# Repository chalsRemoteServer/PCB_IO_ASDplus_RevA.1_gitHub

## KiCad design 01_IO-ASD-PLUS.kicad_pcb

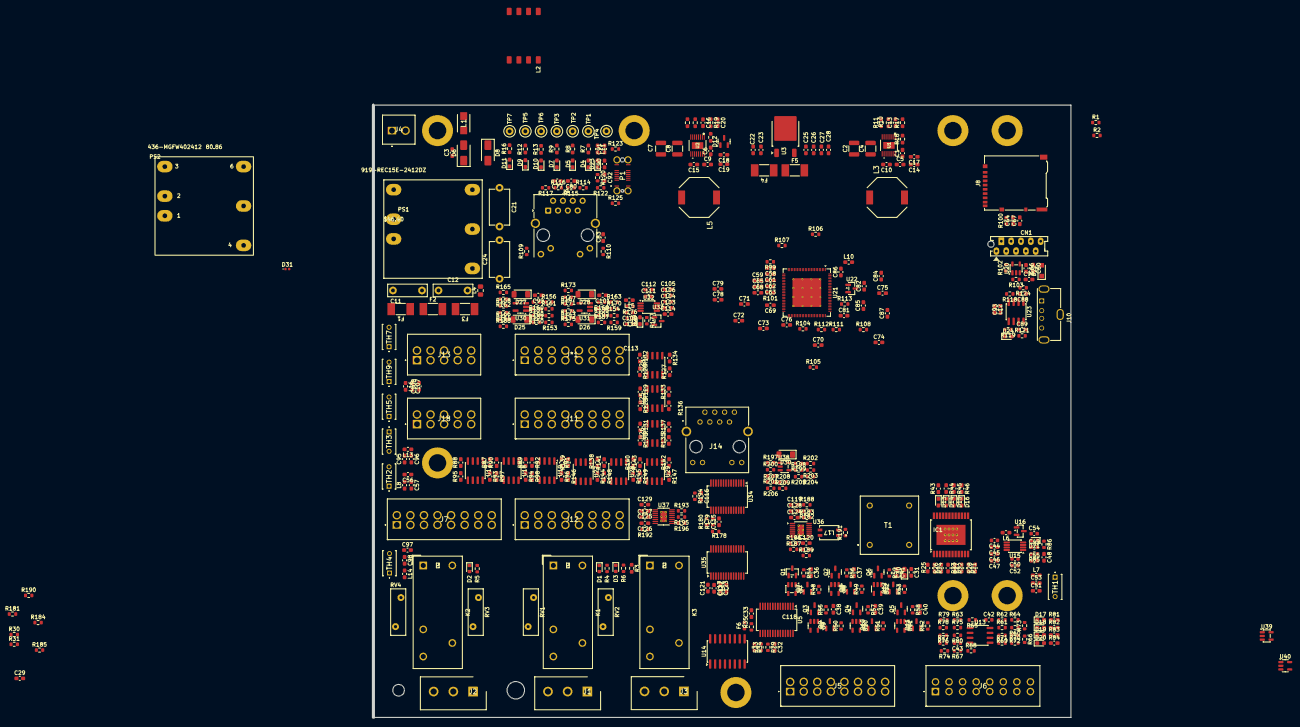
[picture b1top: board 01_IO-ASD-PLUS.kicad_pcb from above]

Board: 2 copper layers, 180.0 x 158.0 mm, 473 parts (0 on the bottom side), 353 nets, no tracks yet.

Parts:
C1, C6, C14, C17, C18, C19, C23, C26, C27, C68: 10uF; C_0603_1608Metric_Pad1.08x0.95mm_HandSolder
C2, C7: 10uF; C_1210_3225Metric
C3, C10, C15, C20, C22, C25, C29, C31, C32, C33, C36, C37, C38, C39, C40, C41, C48, C51, C53, C56, C57, C59, C60, C61, C66, C67, C69, C70, C71, C74, C76, C77, C79, C80, C81, C82, C83, C84, C85, C88, C89, C90, C92, C94, C95, C96, C97, C98, C99, C100, C101, C102, C105, C107, C108, C109, C113, C114, C115, C116, C117, C118, C119, C120, C121, C122, C123, C124, C125, C126, C127, C128, C129: 0.1uF; C_0603_1608Metric_Pad1.08x0.95mm_HandSolder
C4, C8: 1uF; C_1210_3225Metric
C5, C9: 4.7uF; C_0603_1608Metric_Pad1.08x0.95mm_HandSolder
C11, C12: 2.2uF; C_Rect_L10.0mm_W3.0mm_P7.50mm_FKS3_FKP3
C13, C16: 24pF; C_0603_1608Metric_Pad1.08x0.95mm_HandSolder
C21, C24: 1500pF; C_Disc_D9.0mm_W5.0mm_P10.00mm
C28, C62, C65, C75: 0.01uF; C_0603_1608Metric_Pad1.08x0.95mm_HandSolder
C30: 47uF; CP_EIA-1608-10_AVX-L_HandSolder
C42, C43, C46, C52, C54, C55: 0.1uF; C_0603_1608Metric
C44: 22uF; C_0603_1608Metric
C45, C104: 470nF; C_0603_1608Metric
C47, C50, C106, C111: 4.7uF; C_0603_1608Metric
C49, C63, C110: 10uF; C_0603_1608Metric
C58: 1nF; C_0603_1608Metric_Pad1.08x0.95mm_HandSolder
C64, C78: 1uF; C_0603_1608Metric_Pad1.08x0.95mm_HandSolder
C72, C73: 10pF; C_0603_1608Metric_Pad1.08x0.95mm_HandSolder
C86, C87: 18pF; C_0603_1608Metric_Pad1.08x0.95mm_HandSolder
C91: 4.7uF/10v; C_0603_1608Metric_Pad1.08x0.95mm_HandSolder
C93: 150uF/10v; C_0603_1608Metric_Pad1.08x0.95mm_HandSolder
C103: 22uF; C_0603_1608Metric_Pad1.08x0.95mm_HandSolder
C112: 0.1uf; C_0603_1608Metric_Pad1.08x0.95mm_HandSolder
CN1: 10way 1.27mm; MicroMatch_10way_P1.75mm
D1, D2, D3, D21: LED; LED_0603_1608Metric
D4, D5, D7, D9, D10, D11, D13, D14, D15, D16, D17, D18, D19, D20, D23, D24, D29: LED; LED_0603_1608Metric_Pad1.05x0.95mm_HandSolder
D6: SMAJ30CA; D_SMA
D8: MBRA340; D_SMA
D12: SP0502BAHT; SOT-23
D22: PMEG2010BER; Nexperia_CFP3_SOD-123W
D25, D26: BZV55B3V3; D_MiniMELF
D27, D28: BZV55B11; D_MiniMELF
D30: BZV55C15; D_MiniMELF
D31: LED; LED_0402_1005Metric
F1, F2, F3, F4, F5: SF-2410HI050T-2; Fuse_Littelfuse-NANO2-451_453
F6: Fuse_Small; C_0603_1608Metric
IC1: VNI4140K; ST_PowerSSO-24_SlugDown_ThermalVias
J1, J2, J3: 1147330000; 3POS-5.08PITCH
J4: 1604470000; 2POS-PITCH3.5MM
J5, J7, J11, J12: 1728840000; 16POS-2LINEAS-3.5PITCH
J6: 1728840000; 1728840000_17-25
J8: Micro_SD_Card_Det1; microSD_HC_Hirose_DM3AT-SF-PEJM5
J9: RJ45_Wuerth_7499010211A; RJ45_Wuerth_7499010211A_Horizontal
J10: USB_Type A_ Receptacle; USB_A_Molex_105057_Vertical
J13, J18: 1728810000
J14: 8P8C_LED_Shielded; WE-RJ45LAN
J*1: 1728840000; 16POS-2LINEAS-3.5PITCH
K1, K2, K3: G2RL-1-H; Relay_SPDT_Omron_G2RL-1
L1: 3.9uH; INDM4532X320N
L2: SDR0906-3R9ML
L3, L5: 10uH; 744065100
L4: 4.7uH; L_0805_2012Metric_Pad1.15x1.40mm_HandSolder
L6, L15: 0603; L_0603_1608Metric_Pad1.05x0.95mm_HandSolder
L7: 10uH; L_0603_1608Metric_Pad1.05x0.95mm_HandSolder
L8, L10, L11, L12, L13, L14, L16: L_Iron_Small; L_0603_1608Metric_Pad1.05x0.95mm_HandSolder
L17: 200uH; DLW43_MUR
P1: USB_C_Plug_USB2.0; USB4145030070C
PS1: REC15E-2412DZ
PS2: MGFW402412; MGFW400512
Q1, Q2, Q3, Q4, Q5, Q6: MMBT3904; SOT-23
Q7, Q8, Q9, Q10, Q11, Q12: DMP3099L; SOT-23
R1, R2: 2.7K; R_0603_1608Metric
R3: 0 ohms; R_0603_1608Metric_Pad0.98x0.95mm_HandSolder
R4, R5, R6: 1.2k; R_0603_1608Metric
R7: 560ohms; R_0603_1608Metric_Pad0.98x0.95mm_HandSolder
R8: 1k; R_0603_1608Metric_Pad0.98x0.95mm_HandSolder
R9, R12, R13: 2.7k; R_0603_1608Metric_Pad0.98x0.95mm_HandSolder
R10, R14: 33k; R_0603_1608Metric_Pad0.98x0.95mm_HandSolder
R11, R15, R17: 86.5k; R_0603_1608Metric_Pad0.98x0.95mm_HandSolder
R16, R18: 4.7k; R_0603_1608Metric_Pad0.98x0.95mm_HandSolder
R19: 82k; R_0603_1608Metric_Pad0.98x0.95mm_HandSolder
R20: 10k; R_0603_1608Metric_Pad0.98x0.95mm_HandSolder
R21, R22, R23, R24, R25, R26, R27, R28, R93, R94, R95, R96, R97, R98, R132, R133, R134, R135, R136, R137, R144, R145, R146, R147, R148, R149: 4.7k; C_0603_1608Metric_Pad1.08x0.95mm_HandSolder
R29, R60, R63, R66, R69, R71, R72, R76, R77, R78, R79, R100, R101, R107, R118, R119, R150, R154, R178: 10k; R_0603_1608Metric
R30, R31, R33, R34, R35, R179, R180, R181, R184, R185, R186, R187, R188, R189, R190, R192, R193, R194, R198, R199: 0R; R_0603_1608Metric
R43, R44, R45, R46, R81, R82, R83, R84: 10k; C_0603_1608Metric_Pad1.08x0.95mm_HandSolder
R48, R49, R50, R51, R52, R53, R68, R75, R99: 2.2k; R_0603_1608Metric
R54, R55, R56, R57, R58, R59, R64, R73, R86, R177: 1k; R_0603_1608Metric
R61, R65, R151, R152, R153, R155, R156, R157, R158, R159, R160, R161, R162, R163, R164, R165, R166, R167, R168, R169, R170, R171, R172, R173, R174, R175: 10; R_0603_1608Metric
R62, R70, R85, R176, R197: 100; R_0603_1608Metric
R67, R74, R80: 0 ohms; R_0603_1608Metric
R87, R88, R89, R90, R91, R92, R126, R127, R128, R129, R130, R131, R138, R139, R140, R141, R142, R143: 2.2k; C_0603_1608Metric_Pad1.08x0.95mm_HandSolder
R102, R103, R104, R108: 1K; R_0603_1608Metric
R105, R106, R123, R124, R125: 0; R_0603_1608Metric
R109, R110: 160; R_0603_1608Metric
R111, R112: 12k 1%; R_0603_1608Metric
R113: 12.3k 1%; R_0603_1608Metric
R114, R115, R116, R117: 49.9R; R_0603_1608Metric
R120, R121: 470; R_0603_1608Metric
R122: 5.1k 1%; R_0603_1608Metric
R182: 620; R_0603_1608Metric
R183: 1.5K; R_0603_1608Metric
R191: 120 1%; R_0603_1608Metric
R195, R196: 4.7k; R_0603_1608Metric
R200, R201, R202, R203, R204, R205, R206, R207, R208, R209: 100K; R_0603_1608Metric
RV1, RV2, RV3, RV4: Varistor; RV_Disc_D12mm_W3.9mm_P7.5mm
T1: Transformer_1P_1S; TRANFORMADOR_1001C
TH1, TH2, TH3, TH4, TH5, TH7, TH9: B59985C120A70; B59985C0120A070
TP1, TP2, TP3, TP4, TP5, TP6, TP7: TestPoint; TestPoint_Loop_D1.80mm_Drill1.0mm_Beaded
U1: LTC3646EMSEPBF; MSOP-16_MSE
U2: LTC3646E; MSOP-16_MSE
U3: KF33BDT; TO-252-2
U5, U34: MCP23S17_SS; SSOP-28_5.3x10.2mm_P0.65mm
U7, U8, U9, U10, U11, U12: 74LVC1G17; SOT-23-5
U13: TSB582; SO-8_3.9x4.9mm_P1.27mm
U14: ULN2003A; SOIC-16W_5.3x10.2mm_P1.27mm
U15, U32: LM7705; VSSOP-8_3x3mm_P0.65mm
U16, U33: MCP1799T-5002H/TT; SOT-23
U17, U18, U19, U24, U25, U26, U27, U28, U29: ILD206T; SOIC-8_3.9x4.9mm_P1.27mm
U20: 24AA02E-OT; SOT-23-5
U21: FT900Q; ArtInChip_QFN-100-1EP_12x12mm_P0.4mm_EP7.4x7.4mm_ThermalVias
U22: MCP9700Ax-ETT; SOT-23
U23: TPS2024; SOIC-8_3.9x4.9mm_P1.27mm
U30, U31: TLV9301xDBV; SOT-23-5_HandSoldering
U35: MAX3232; SSOP-28_5.3x10.2mm_P0.65mm
U36: LTC6820; MSOP-16-1EP_3x4.039mm_P0.5mm_EP1.651x2.845mm_ThermalVias
U37: MAX3232; MSOP-16-1EP_3x4.039mm_P0.5mm_EP1.651x2.845mm_ThermalVias
U38: TLV2371DBV; SOT-23-5
U39: TLV702475_SOT23-5; SOT-23-5
U40: 74LS30; SOT-23-5

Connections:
+1.2Vreg: C61.1, C62.1, C63.1, C76.1, C78.1, C79.1, U21.32 (FSOURCE), U21.63 (VOUT1), U21.67 (VCC1V2), U21.77 (VOUT2)
+3.3V: C25.1, C26.1, C27.1, C28.1, C66.1, C83.1, F4.1, F5.1, J9.4 (CTD), J9.5 (CRD), R7.2, R21.2, R22.2, R23.2, R24.2, R93.1, R94.1, R95.1, R96.1, R97.1, R98.1, R99.2, R102.2, R103.2, R109.2, R110.2, R118.2, R119.2, R132.1, R133.1, R134.1, R135.1, R136.1, R137.1, R144.1, R145.1, R146.1, R147.1, R148.1, R149.1, TP1.1, U3.3 (VO), U20.4 (V_{CC}), U22.1 (V_{DD})
+3.3v: C33.1, C116.1, R1.1, R2.1, R29.2, R30.1, R31.2, R34.2, R178.2, R179.1, R180.1, R195.1, R196.1, U5.9 (VDD), U34.9 (VDD)
+3.3v_Fuse: C59.1, C64.1, C65.1, C67.1, C68.1, C69.1, C70.1, C75.1, C81.1, C82.1, C84.1, C85.1, C100.1, C101.1, F4.2, J8.4 (VDD), R100.1, R107.1, U21.33 (VPP), U21.46 (VCCIO3V3), U21.64 (VCCIO3V3), U21.68 (VUSB3V3), U21.76 (VETH3V3), U21.79 (VETH3V3), U21.95 (VCC3V3A)
+3.3v_Fuse3: C118.1, C120.2, C124.1, R184.2, R185.2, R189.2, R190.2, U36.1 (EN), U36.6 (VDDs), U36.9 (VDD)
+3.3v_Fuse_comm: C119.1, C128.1, F5.2, U35.16 (VCC), U37.16 (VCC)
+5V: C16.1, C18.1, C19.1, C20.1, C22.1, C23.1, C88.2, D12.1 (K), D12.2 (K), D22.1 (K), L5.2, R8.2, R19.2, TP2.1, U2.5 (VON), U3.1 (VI), U7.5 (VCC), U8.5 (VCC), U9.5 (VCC), U10.5 (VCC), U11.5 (VCC), U12.5 (VCC), U23.2 (IN)
+10V: C13.1, C14.1, C17.1, L3.2, R9.2, R17.2, TP3.1, U1.5 (VON)
+12V: C42.1, C55.1, C99.2, C114.1, R12.2, R164.1, R172.1, TP5.1, U13.8 (VCC+), U16.3 (VI), U30.5 (V+), U31.5 (V+), U33.3 (VI)
+24V: C1.1, C2.1, C4.1, C6.1, C7.1, C8.1, C30.1, C31.2, C36.2, C37.2, C38.2, C39.2, C40.2, C41.2, C48.2, F1.1, F2.1, F6.2, IC1.1 (VCC_1), IC1.25 (VCC_2), J14.7, L2.4, Q7.2 (S), Q8.2 (S), Q9.2 (S), Q10.2 (S), Q11.2 (S), Q12.2 (S), R3.2, R16.2, R48.2, R49.2, R50.2, R51.2, R52.2, R53.2, R199.1, R202.1, R206.1, TH1.1, TH2.2, TH3.2, TH4.2, TH5.2, TH7.2, TH9.2, TP7.1, U1.9 (PVIN_2), U1.10 (PVIN), U1.16 (SVIN), U2.9 (PVIN_2), U2.10 (PVIN), U2.15 (RUN), U2.16 (SVIN)
+24VDC: C3.1, D6.1 (A1), D8.2 (A), J4.2
+VBUS_IN: C90.2, C91.1, D23.2 (A), L11.2, R104.1
+VBUS_OUT: C89.1, C93.1, D24.2 (A), L12.2, R108.1, U23.6 (OUT)
-12V: R13.2, TP6.1
-12V_Analog: C1.2, C2.2, C4.2, C5.2, C6.2, C7.2, C8.2, C9.2, C11.2, C12.2, C14.2, C17.2, C18.2, C19.2, C20.2, C21.1, C22.2, C23.2, C25.2, C26.2, C27.2, C28.2, C29.2, C30.2, C31.1, C32.2, C33.2, C36.1, C37.1, C38.1, C39.1, C40.1, C41.1, C42.2, C43.2, C44.2, C45.2, C46.2, C47.2, C48.1, C49.2, C51.2, C53.2, C54.2, C55.2, C56.1, C57.1, C58.2, C59.2, C60.2, C61.2, C62.2, C63.2, C64.2, C65.2, C66.2, C67.2, C68.2, C69.2, C70.2, C71.2, C72.2, C73.2, C74.2, C75.2, C76.2, C77.1, C78.2, C79.2, C80.2, C81.2, C82.2, C83.2, C84.2, C85.2, C86.1, C87.2, C88.1, C89.2, C90.1, C91.2, C92.1, C93.2, C94.1, C95.1, C96.1, C97.1, C98.1, C99.1, C100.2, C101.2, C102.2, C103.2, C104.2, C105.2, C106.2, C107.1, C108.1, C109.2, C110.2, C113.2, C114.2, C115.2, C116.2, C118.2, C119.2, C120.1, C121.1, C122.1, C124.2, C125.2, C126.2, C128.2, CN1.7, D4.1 (K), D5.1 (K), D7.1 (K), D9.1 (K), D10.1 (K), D11.1 (K), D12.3 (A), D25.2 (A), D26.2 (A), D27.2 (A), D28.2 (A), D30.2 (A), F3.2, IC1.6 (GND), J5.6 (MZ), J6.25 (GND), J6.26 (GND), J6.27 (GND), J6.28 (GND), J7.9, J7.11, J7.12, J7.14, J7.16, J8.6 (VSS), J8.10 (SHIELD), J9.8, J9.SH, J10.4 (GND), J11.9, J11.11, J11.12, J11.14, J11.16, J12.9, J12.11, J12.12, J12.14, J12.16, J13.2 (X5), J13.9 (X4), J14.8, J14.12, J18.2 (X5), J18.9 (X4), J*1.9, J*1.11, J*1.12, J*1.14, J*1.16, L1.2, L10.1, PS1.2 (-Vin), Q1.2 (E), Q2.2 (E), Q3.2 (E), Q4.2 (E), Q5.2 (E), Q6.2 (E), R10.1, R14.1, R18.1, R20.1, R25.1, R26.1, R27.1, R28.1, R30.2, R33.1, R35.1, R43.1, R44.1, R45.1, R46.1, R54.1, R55.1, R56.2, R57.1, R58.1, R59.1, R60.1, R63.1, R74.2, R80.2, R85.1, R86.2, R101.2, R111.2, R112.2, R113.2, R120.2, R121.2, R122.2, R123.1, R124.1, R125.1, R150.1, R154.1, R166.2, R168.2, R174.2, R175.2, R176.2, R177.1, R181.2, R182.2, R186.2, R187.2, R188.1, R194.2, R205.2, R209.2, TP4.1, U1.1 (SGND), U1.7 (MODE/SYNC), U1.14 (EXTVCC), U1.17 (PGND), U2.1 (SGND), U2.7 (MODE/SYNC), U2.14 (EXTVCC), U2.17 (PGND), U3.2 (GND), U5.10 (VSS), U7.3 (GND), U8.3 (GND), U9.3 (GND), U10.3 (GND), U11.3 (GND), U12.3 (GND), U14.8 (GND), U15.2 (GND), U15.5 (GND), U16.1 (GND), U17.2 (C_1), U17.4 (C_2), U17.5 (E_1), U17.7 (E_2), U18.2 (C_1), U18.4 (C_2), U18.5 (E_1), U18.7 (E_2), U19.2 (C_1), U19.4 (C_2), U19.5 (E_1), U19.7 (E_2), U20.2 (V_{SS}), U21.45 (GND), U22.3 (GND), U23.1 (GND), U24.2 (C_1), U24.4 (C_2), U24.5 (E_1), U24.7 (E_2), U25.2 (C_1), U25.4 (C_2), U25.5 (E_1), U25.7 (E_2), U26.2 (C_1), U26.4 (C_2), U26.5 (E_1), U26.7 (E_2), U27.2 (C_1), U27.4 (C_2), U27.5 (E_1), U27.7 (E_2), U28.2 (C_1), U28.4 (C_2), U28.5 (E_1), U28.7 (E_2), U29.2 (C_1), U29.4 (C_2), U29.5 (E_1), U29.7 (E_2), U32.2 (GND), U32.5 (GND), U33.1 (GND), U34.10 (VSS), U34.17 (A2), U35.15 (GND), U36.14 (GND), U37.15 (GND), U38.2 (V-)
/ENTRADAS1/Error_Conn_Entrada_+24v: C96.2, J11.1, J11.3, J11.4, J11.6, J11.8, L13.1
/ENTRADAS1/opto_out1: R132.2, U24.8 (C_4), U34.5 (GPB4)
/ENTRADAS1/opto_out2: R134.2, U24.6 (C_3), U34.7 (GPB6)
/ENTRADAS1/opto_out3: R133.2, U25.8 (C_4), U34.6 (GPB5)
/ENTRADAS1/opto_out4: R136.2, U25.6 (C_3), U34.8 (GPB7)
/ENTRADAS1/opto_out5: R135.2, U26.8 (C_4), U34.21 (GPA0)
/ENTRADAS1/opto_out6: R137.2, U26.6 (C_3), U34.22 (GPA1)
/ENTRADAS2/Error_Conn_Entrada_+24v: C98.2, J12.1, J12.3, J12.4, J12.6, J12.8, L14.1
/ENTRADAS2/opto_out1: R144.2, U27.8 (C_4)
/ENTRADAS2/opto_out2: R146.2, U27.6 (C_3), U34.1 (GPB0)
/ENTRADAS2/opto_out3: R145.2, U28.8 (C_4)
/ENTRADAS2/opto_out4: R148.2, U28.6 (C_3), U34.2 (GPB1)
/ENTRADAS2/opto_out5: R147.2, U29.8 (C_4), U34.3 (GPB2)
/ENTRADAS2/opto_out6: R149.2, U29.6 (C_3), U34.4 (GPB3)
/ENTRADAS/Error_Conn_Entrada_+24v: C57.2, J7.1, J7.3, J7.4, J7.6, J7.8, L8.1
/ENTRADAS/opto_out1: R93.2, U17.8 (C_4), U34.23 (GPA2)
/ENTRADAS/opto_out2: R95.2, U17.6 (C_3), U34.25 (GPA4)
/ENTRADAS/opto_out3: R94.2, U18.8 (C_4), U34.24 (GPA3)
/ENTRADAS/opto_out4: R97.2, U18.6 (C_3), U34.26 (GPA5)
/ENTRADAS/opto_out5: R96.2, U19.8 (C_4), U34.27 (GPA6)
/ENTRADAS/opto_out6: R98.2, U19.6 (C_3), U34.28 (GPA7)
/Ent Especial/AN0_POT: D26.1 (K), R154.2, R155.2, U21.88 (ADC2/CAM_PCLK/GPIO7)
/Ent Especial/AN1_POT: D25.1 (K), R150.2, R151.2, U21.89 (ADC3/CAM_VD/GPIO8)
/Ent Especial/Error_Conn_Entrada_ESP+24v: C108.2, J*1.1, J*1.2, J*1.3, J*1.4, J*1.6, J*1.8, L16.1
/Error/24v_in1: C51.1, J6.29 (24V), J6.30 (24V), J6.31 (LT5), J6.32 (LT6), L7.1, R81.1, R82.1, R83.1, R84.1
/Error/24v_in2: F6.1, U14.9 (COM)
/Port Expansor/MISO_SPI: R1.2, U5.14 (SO), U21.14 (SPIM_MISO/GPIO30), U34.14 (SO), U36.3 (MISO)
/Port Expansor/MOSI_SPI: R2.2, U5.13 (SI), U21.13 (SPIM_MOSI/GPIO29), U34.13 (SI), U36.2 (MOSI)
/Port Expansor/SCK_SPI: U5.12 (SCK), U21.11 (SPIM_CLK/GPIO27), U34.12 (SCK), U36.4 (SCKL)
/Processador/!CS_J5_J6: U5.11 (~CS), U21.18 (SPIM_SS2/GPIO34)
/Processador/BUSY_DISPLAY: U21.44 (UART0_RI/UART1_CTS/PWM7/GPIO55), U37.11 (T1IN)
/Processador/DAC0: R71.2, U21.98 (DAC0/CAM_D3/GPIO14)
/Processador/DAC1: R79.2, U21.97 (DAC1/CAM_D4/GPIO13)
/Processador/INTA_J5_J6: U5.20 (INTA), U21.48 (PWM1/GPIO57)
/Processador/INT_FT812: R195.2, R196.2, U21.40 (UART0_CTS/GPIO51), U21.49 (PWM2/GPIO58), U37.10 (T2IN), U37.12 (R1OUT)
/Processador/METAL_INTERRUPCION: U21.43 (UART0_DCD/UART1_RTS/PWM6/GPIO54), U37.9 (R2OUT)
/Processador/MO1: IC1.10 (IN4), R28.2, U21.47 (PWM0/GPIO56)
/Processador/MO2: IC1.8 (IN3), R27.2, U21.1 (CAN1_TXD/CAM_D0/GPIO17)
/Processador/MO3: IC1.4 (IN2), R26.2, U21.2 (CAN1_RXD/GPIO18)
/Processador/MO4: IC1.2 (IN1), R25.2, U21.93 (ADC7/CAM_D5/GPIO12)
/Processador/Metal1: U14.5 (I5), U21.99 (CAN0_TXD/CAM_D2/GPIO15)
/Processador/Metal2: U14.6 (I6), U21.100 (CAN0_RXD/CAM_D1/GPIO16)
/Processador/SPIM_SS: U21.19 (SPIM_SS3/GPIO35), U36.5 (!CS)
/Processador/UART0_RXD: U21.38 (UART0_RXD/GPIO49), U35.9 (R2OUT)
/Processador/UART0_TXD: U21.37 (UART0_TXD/GPIO48), U35.10 (T2IN)
/Processador/UART1_RXD: U21.42 (UART0_DSR/UART1_RXD/PWM5/GPIO53), U35.12 (R1OUT)
/Processador/UART1_TXD: U21.41 (UART0_DTR/UART1_TXD/PWM4/GPIO52), U35.11 (T1IN)
/Processador/USB_D+_Device: P1.A6 (D+), U21.70 (D_DP)
/Processador/USB_D-_Device: P1.A7 (D-), U21.69 (D_DM)
/Reles/FAULT_RELE: D3.1 (K), K3.A2, U14.10 (O7)
/Reles/METAL1_RELE: D1.1 (K), K1.A2, U14.12 (O5)
/Reles/METAL2_RELE: D2.1 (K), K2.A2, U14.11 (O6)
/Serial_Comm/600mA: R182.1, R183.2, U36.15 (ICMP)
/Serial_Comm/+2.0v: R183.1, U36.16 (IBIAS)
/Serial_Comm/Led_ctrl/INT: J14.6, R193.1, R200.2, R201.2, U37.13 (R1IN)
/Serial_Comm/Led_ctrl/LED1_A: J14.10, J14.11
/Serial_Comm/Led_ctrl/LED1_C: J14.9, R197.1
/USB/USB_Current_Status: R119.1, U23.5 (!OC)
/USB/USB_Power_Switcher: R118.1, U23.4 (!_ENABLE)
AGND: C24.2, F3.1, PS1.5 (Com)
DBG_5V: C60.1, CN1.9, D22.2 (A)
unnamed: C74.1, U21.86 (VDDBAT)
unnamed: C11.1, C12.1, F1.2, F2.2, L4.1
unnamed: C53.1, L7.2, TH1.2
unnamed: C56.2, L8.2, TH2.1
unnamed: C72.1, R105.1
unnamed: C73.1, R106.1
unnamed: C77.2, R116.1, R117.1
unnamed: C80.1, R114.1, R115.1
unnamed: C92.2, L11.1, P1.A4 (VBUS)
unnamed: C95.2, L13.2, TH3.1
unnamed: C97.2, L14.2, TH4.1
unnamed: C107.2, L16.2, TH5.1
unnamed: D1.2 (A), R4.1
unnamed: D2.2 (A), R5.1
unnamed: D3.2 (A), R6.1
unnamed: D4.2 (A), R7.1
unnamed: D5.2 (A), R8.1
unnamed: C3.2, D6.2 (A2), J4.1, L1.1
unnamed: D7.2 (A), R9.1
unnamed: D8.1 (K), L2.1
unnamed: D9.2 (A), R12.1
unnamed: D10.2 (A), R13.1
unnamed: D11.2 (A), R16.1
unnamed: D13.2 (A), IC1.22 (OUT1_1), IC1.23 (OUT1_2), IC1.24 (OUT1_3), J6.17 (MO1)
unnamed: D13.1 (K), R43.2
unnamed: D14.2 (A), IC1.19 (OUT2_1), IC1.20 (OUT2_2), IC1.21 (OUT2_3), J6.18 (MO2)
unnamed: D14.1 (K), R44.2
unnamed: D15.2 (A), IC1.16 (OUT3_1), IC1.17 (OUT3_2), IC1.18 (OUT3_3), J6.19 (MO3)
unnamed: D15.1 (K), R45.2
unnamed: D16.2 (A), IC1.13 (OUT4_1), IC1.14 (OUT4_2), IC1.15 (OUT4_3), J6.20 (MO4)
unnamed: D16.1 (K), R46.2
unnamed: D17.2 (A), R81.2
unnamed: D17.1 (K), J6.21 (LT1), U14.16 (O1)
unnamed: D18.2 (A), R82.2
unnamed: D18.1 (K), J6.22 (LT2), U14.15 (O2)
unnamed: D19.2 (A), R83.2
unnamed: D19.1 (K), D20.1 (K), J6.23 (LT3), U14.14 (O3)
unnamed: D20.2 (A), R84.2
unnamed: C49.1, C54.1, D21.2 (A), U15.4 (VDD), U16.2 (VO)
unnamed: D21.1 (K), R86.1
unnamed: D23.1 (K), R120.1
unnamed: D24.1 (K), R121.1
unnamed: D27.1 (K), J*1.5, R160.1
unnamed: D28.1 (K), J*1.7, R169.1
unnamed: C109.1, C110.1, C113.1, D29.2 (A), U32.4 (VDD), U33.2 (VO)
unnamed: D29.1 (K), R177.2
unnamed: D30.1 (K), R199.2, U38.5 (V+)
unnamed: IC1.3 (STAT1), R24.1, U5.7 (GPB6)
unnamed: IC1.5 (STAT2), R23.1, U5.8 (GPB7)
unnamed: IC1.7 (STAT3), R22.1, U5.21 (GPA0)
unnamed: IC1.9 (STAT4), R21.1, U5.22 (GPA1)
unnamed: J1.1, K1.12, RV1.1
unnamed: J1.2, K1.11, RV1.2, RV2.2
unnamed: J1.3, K1.14, RV2.1
unnamed: J2.1, K2.12, RV3.1
unnamed: J2.2, K2.11, RV3.2, RV4.2
unnamed: J2.3, K2.14, RV4.1
unnamed: J3.1, K3.12
unnamed: J3.2, K3.11
unnamed: J3.3, K3.14
unnamed: J5.1 (DA0), J5.9 (GND), J5.10 (GND), J5.11 (GND), J5.12 (GND), J5.13 (GND), R63.2, R65.2
unnamed: J5.7 (ICM), J5.8 (OUT2), R70.2
unnamed: J6.24 (LT4), U14.13 (O4)
unnamed: J7.2, R88.1
unnamed: J7.5, R87.1
unnamed: J7.7, R92.1
unnamed: J7.10, R89.1
unnamed: J7.13, R90.1
unnamed: J7.15, R91.1
unnamed: J8.5 (CLK), U21.3 (SD_CLK/GPIO19)
unnamed: J8.3 (CMD), U21.4 (SD_CMD/GPIO20)
unnamed: J8.7 (DAT0), U21.8 (SD_DATA0/GPIO24)
unnamed: J8.8 (DAT1), U21.7 (SD_DATA1/GPIO23)
unnamed: J8.1 (DAT2), U21.6 (SD_DATA2/GPIO22)
unnamed: J8.2 (DAT3/CD), U21.5 (SD_DATA3/GPIO21)
unnamed: J8.9 (DET), R100.2, U21.9 (SD_CD/GPIO25)
unnamed: J9.9, R109.1
unnamed: J9.12, R110.1
unnamed: J9.3 (RD+), R115.2, U21.80 (RXIP)
unnamed: J9.6 (RD-), R114.2, U21.81 (RXIN)
unnamed: J9.1 (TD+), R117.2, U21.82 (TXOP)
unnamed: J9.2 (TD-), R116.2, U21.83 (TXON)
unnamed: J10.5 (Shield), R124.2
unnamed: C94.2, J10.1 (VBUS), L12.1
unnamed: J11.2, R127.1
unnamed: J11.5, R126.1
unnamed: J11.7, R131.1
unnamed: J11.10, R128.1
unnamed: J11.13, R129.1
unnamed: J11.15, R130.1
unnamed: J12.2, R139.1
unnamed: J12.5, R138.1
unnamed: J12.7, R143.1
unnamed: J12.10, R140.1
unnamed: J12.13, R141.1
unnamed: J12.15, R142.1
unnamed: J13.1 (X0), U35.14 (T1OUT)
unnamed: J13.3 (X1), U35.7 (T2OUT)
unnamed: J13.5 (X2), U35.13 (R1IN)
unnamed: J13.7 (X3), U35.8 (R2IN)
unnamed: J13.4 (X6), U37.8 (R2IN)
unnamed: J13.6 (X7), U37.14 (T1OUT)
unnamed: J13.8 (X8), R192.2
unnamed: J13.10 (X9), R193.2
unnamed: J14.SH, R194.1
unnamed: K1.A1, K2.A1, K3.A1, R3.1, R4.2, R5.2, R6.2
unnamed: L10.2, U21.74 (AGND)
unnamed: P1.A5 (CC), R122.1
unnamed: P1.A1 (GND), R123.2
unnamed: P1.S1 (SHIELD), R125.2
unnamed: C24.1, L4.2, PS1.1 (+Vin)
unnamed: C21.2, PS1.4 (-Vo)
unnamed: Q1.1 (B), U7.4
unnamed: Q1.3 (C), Q7.1 (G), R48.1
unnamed: Q2.1 (B), U8.4
unnamed: Q2.3 (C), Q8.1 (G), R49.1
unnamed: Q3.1 (B), U9.4
unnamed: Q3.3 (C), Q9.1 (G), R50.1
unnamed: Q4.1 (B), U10.4
unnamed: Q5.1 (B), U11.4
unnamed: Q6.1 (B), U12.4
unnamed: Q7.3 (D), R54.2
unnamed: Q8.3 (D), R55.2
unnamed: Q9.3 (D), R56.1
unnamed: Q10.3 (D), R57.2
unnamed: Q4.3 (C), Q10.1 (G), R51.1
unnamed: Q11.3 (D), R58.2
unnamed: Q5.3 (C), Q11.1 (G), R52.1
unnamed: Q12.3 (D), R59.2
unnamed: Q6.3 (C), Q12.1 (G), R53.1
unnamed: R60.2, R61.2
unnamed: R62.2, R64.1
unnamed: R64.2, R66.1
unnamed: R66.2, R69.2
unnamed: R68.1, R69.1, R72.2
unnamed: R70.1, R73.2
unnamed: R72.1, R74.1
unnamed: R73.1, R77.2
unnamed: R75.1, R76.1, R78.2
unnamed: R76.2, R77.1
unnamed: R78.1, R80.1
unnamed: R151.1, R152.1, U30.1
unnamed: R152.2, R153.2
unnamed: R153.1, R156.2
unnamed: R155.1, R157.1, U31.1
unnamed: R156.1, R161.2
unnamed: R157.2, R159.2
unnamed: R158.1, R161.1, R162.2
unnamed: R159.1, R163.2
unnamed: R162.1, R165.2, R166.1, R168.1
unnamed: R163.1, R170.2
unnamed: R164.2, R165.1
unnamed: R167.1, R170.1, R171.2
unnamed: R171.1, R173.2, R174.1, R175.1
unnamed: R172.2, R173.1
unnamed: R197.2, R198.2, U38.1
unnamed: R202.2, R203.1
unnamed: R204.1, R205.1
unnamed: R206.2, R207.1
unnamed: R208.1, R209.1
unnamed: L17.4, R191.2, T1.1 (AA)
unnamed: L17.1, R191.1, T1.2 (AB)
unnamed: J14.1, T1.3 (SA)
unnamed: J14.2, T1.4 (SB)
unnamed: C10.1, U1.12 (BOOST)
unnamed: C5.1, R11.1, U1.3 (ITH), U1.13 (INTVCC)
unnamed: R11.2, U1.6 (PGOOD)
unnamed: R10.2, U1.4 (RT)
unnamed: C10.2, L3.1, U1.11 (SW)
unnamed: C13.2, R17.1, R18.2, U1.2 (VFB)
unnamed: C15.1, U2.12 (BOOST)
unnamed: C9.1, R15.1, U2.3 (ITH), U2.13 (INTVCC)
unnamed: R15.2, U2.6 (PGOOD)
unnamed: R14.2, U2.4 (RT)
unnamed: C15.2, L5.1, U2.11 (SW)
unnamed: C16.2, R19.1, R20.2, U2.2 (VFB)
unnamed: R31.1, R35.2, U5.15 (A0)
unnamed: R34.1, U5.16 (A1)
unnamed: R33.2, U5.17 (A2)
unnamed: U5.1 (GPB0), U11.2
unnamed: U5.2 (GPB1), U12.2
unnamed: U5.3 (GPB2), U10.2
unnamed: U5.4 (GPB3), U8.2
unnamed: U5.5 (GPB4), U9.2
unnamed: U5.6 (GPB5), U7.2
unnamed: C32.1, R29.1, U5.18 (~RESET)
unnamed: R79.1, U13.3 (IN1+)
unnamed: R75.2, U13.2 (IN1-)
unnamed: J5.15 (GND), R65.1, U13.1 (OUT1)
unnamed: C43.1, L6.2, R67.1, U13.4 (VCC-)
unnamed: R71.1, U13.5 (IN2+)
unnamed: R68.2, U13.6 (IN2-)
unnamed: R61.1, R62.1, U13.7 (OUT2)
unnamed: U5.23 (GPA2), U14.1 (I1)
unnamed: U5.24 (GPA3), U14.2 (I2)
unnamed: U5.25 (GPA4), U14.3 (I3)
unnamed: U5.26 (GPA5), U14.4 (I4)
unnamed: U5.27 (GPA6), U14.7 (I7)
unnamed: C50.1, C52.1, U15.1 (CF+)
unnamed: C50.2, C52.2, U15.8 (CF-)
unnamed: C46.1, C47.1, U15.7 (CRES)
unnamed: R85.2, U15.3 (SD)
unnamed: C44.1, C45.1, L6.1, U15.6 (VOUT)
unnamed: R87.2, U17.1 (A_1)
unnamed: R88.2, U17.3 (A_2)
unnamed: R89.2, U18.1 (A_1)
unnamed: R90.2, U18.3 (A_2)
unnamed: R91.2, U19.1 (A_1)
unnamed: R92.2, U19.3 (A_2)
unnamed: R102.1, U20.1 (SCL), U21.30 (I2C1_SCL/GPIO46)
unnamed: R103.1, U20.3 (SDA), U21.31 (I2C1_SDA/GPIO47)
unnamed: U21.87 (ADC1/CAM_XCLK/GPIO6), U22.2 (V_{OUT})
unnamed: C71.1, R107.2, U21.96 (DAC_REFP)
unnamed: CN1.8, U21.36 (DEBUG)
unnamed: R112.1, U21.71 (DRREF)
unnamed: J9.11, U21.61 (ENET_LED0/GPIO4)
unnamed: J9.10, U21.62 (ENET_LED1/GPIO5)
unnamed: R113.1, U21.78 (EREFSET)
unnamed: R111.1, U21.75 (HRREF)
unnamed: C58.1, CN1.10, R99.1, U21.34 (RESETN)
unnamed: R106.2, U21.84 (RTC_XIO)
unnamed: R105.2, U21.85 (RTC_XI/RTC_CLKIN)
unnamed: CN1.1, U21.20 (SPIS0_CLK/GPIO36)
unnamed: CN1.4, U21.23 (SPIS0_MISO/GPIO39)
unnamed: CN1.3, U21.22 (SPIS0_MOSI/GPIO38)
unnamed: CN1.2, U21.21 (SPIS0_SS/GPIO37)
unnamed: R101.1, U21.35 (STESTRESTN)
unnamed: R104.2, U21.60 (VBUS_DTC/GPIO3)
unnamed: R108.2, U21.57 (VBUS__DISCHG/_GPIO0)
unnamed: C86.2, U21.66 (XIO)
unnamed: C87.1, U21.65 (XI/CLKIN)
unnamed: R126.2, U24.1 (A_1)
unnamed: R127.2, U24.3 (A_2)
unnamed: R128.2, U25.1 (A_1)
unnamed: R129.2, U25.3 (A_2)
unnamed: R130.2, U26.1 (A_1)
unnamed: R131.2, U26.3 (A_2)
unnamed: R138.2, U27.1 (A_1)
unnamed: R139.2, U27.3 (A_2)
unnamed: R140.2, U28.1 (A_1)
unnamed: R141.2, U28.3 (A_2)
unnamed: R142.2, U29.1 (A_1)
unnamed: R143.2, U29.3 (A_2)
unnamed: R160.2, U30.3 (+)
unnamed: R158.2, U30.4 (-)
unnamed: L15.2, U30.2 (V-), U31.2 (V-)
unnamed: R169.2, U31.3 (+)
unnamed: R167.2, U31.4 (-)
unnamed: C111.1, C112.1, U32.1 (CF+)
unnamed: C111.2, C112.2, U32.8 (CF-)
unnamed: C105.1, C106.1, U32.7 (CRES)
unnamed: R176.1, U32.3 (SD)
unnamed: C103.1, C104.1, L15.1, U32.6 (VOUT)
unnamed: R180.2, R181.1, U34.15 (A0)
unnamed: R179.2, U34.16 (A1)
unnamed: C115.1, R178.1, U34.18 (~RESET)
unnamed: C117.1, U35.1 (C1+)
unnamed: C117.2, U35.3 (C1-)
unnamed: C123.1, U35.4 (C2+)
unnamed: C123.2, U35.5 (C2-)
unnamed: C121.2, U35.2 (VS+)
unnamed: C122.2, U35.6 (VS-)
unnamed: L17.2, U36.10 (IM)
unnamed: L17.3, U36.11 (IP)
unnamed: R189.1, U36.12 (MSTR)
unnamed: R184.1, R186.1, U36.8 (PHA)
unnamed: R187.1, U36.7 (POL)
unnamed: R188.2, R190.1, U36.13 (SLOW)
unnamed: C129.1, U37.1 (C1+)
unnamed: C129.2, U37.3 (C1-)
unnamed: C127.1, U37.4 (C2+)
unnamed: C127.2, U37.5 (C2-)
unnamed: J14.3, R192.1, U37.7 (T2OUT)
unnamed: C125.1, U37.2 (VS+)
unnamed: C126.1, U37.6 (VS-)
unnamed: R200.1, R207.2, R208.2, U38.3 (+)
unnamed: R198.1, R201.1, R203.2, R204.2, U38.4 (-)

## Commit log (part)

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2026-05-07 respadp de pcb 6 may 26
2026-05-07 7-mayo-2026 831am
2026-05-07 7-may-26 346
    se esta trabajando en los reles esquematico y pcb
2026-05-13 13-Mayo26 se agrego hoja de procesador y USB
    hoja de USB AL 95% HOJA DEL procesador al 75%
2026-05-14 14-Mayo-26
    se agregaron varias sheet de esquematico crecio al 80% la parte de esquematico
2026-05-15 15-mayo-26
    15 mayo 26
2026-05-16 15-may-26
2026-05-19 pcb 18 may 26
    falta poner la fuente de +12/ ya esta casi todo
2026-05-22 22 mayo 26 actualizacion
    se actualizo la PCB para la rama laptop Antigua
2026-05-27 26-05-26
2026-06-05 05/06/26
2026-06-08 08-06-26
2026-06-26 22-jun-24
